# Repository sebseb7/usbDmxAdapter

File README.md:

usbDmxAdapter
=============

usbDmxAdapter

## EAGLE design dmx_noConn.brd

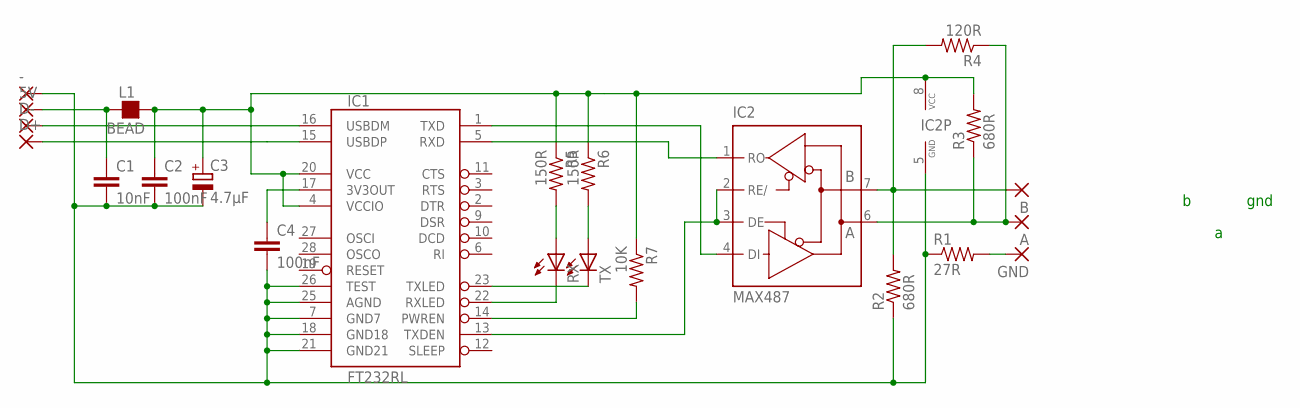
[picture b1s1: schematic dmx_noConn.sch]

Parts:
5V: SMD5; SMD2,54-5,08
-: SMD5; SMD2,54-5,08
A: SMD5; SMD2,54-5,08
B: SMD5; SMD2,54-5,08
C1: 10nF; 0805
C2, C4: 100nF; 0805
C3: 4.7µF; SMC_C
D+: SMD5; SMD2,54-5,08
D-: SMD5; SMD2,54-5,08
GND: SMD5; SMD2,54-5,08
IC1: FT232RL; SSOP28DB
IC2: MAX487; SO08
L1: BEAD; L0805
R1: 27R; 0805
R2, R3: 680R; 0805
R4: 120R; 0805
R5, R6: 150R; 0805
R7: 10K; 0805
RX: LEDCHIP-LED0805; CHIP-LED0805
TX: LEDCHIP-LED0805; CHIP-LED0805

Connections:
+USB_SIEVED: C2.1, C3.+, IC1.4 (VCCIO), IC1.20 (VCC), IC2.8 (VCC), L1.2, R3.2, R5.1, R6.1, R7.1
GND_USB: -.1, C1.2, C2.2, C3.-, C4.2, IC1.7 (GND7), IC1.18 (GND18), IC1.21 (GND21), IC1.25 (AGND), IC1.26 (TEST), IC2.5 (GND), R1.1, R2.1
unnamed: IC1.13 (TXDEN), IC2.2 (RE/), IC2.3 (DE)
unnamed: GND.1, R1.2
unnamed: IC1.5 (RXD), IC2.1 (RO)
unnamed: IC1.1 (TXD), IC2.4 (DI)
unnamed: B.1, IC2.7 (B), R2.2, R4.2
unnamed: A.1, IC2.6 (A), R3.1, R4.1
unnamed: D-.1, IC1.16 (USBDM)
unnamed: D+.1, IC1.15 (USBDP)
unnamed: R5.2, RX.A
unnamed: R6.2, TX.A
unnamed: IC1.22 (RXLED), RX.C
unnamed: IC1.23 (TXLED), TX.C
unnamed: C4.1, IC1.17 (3V3OUT)
unnamed: 5V.1, C1.1, L1.1
unnamed: IC1.14 (PWREN), R7.2

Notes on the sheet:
gnd

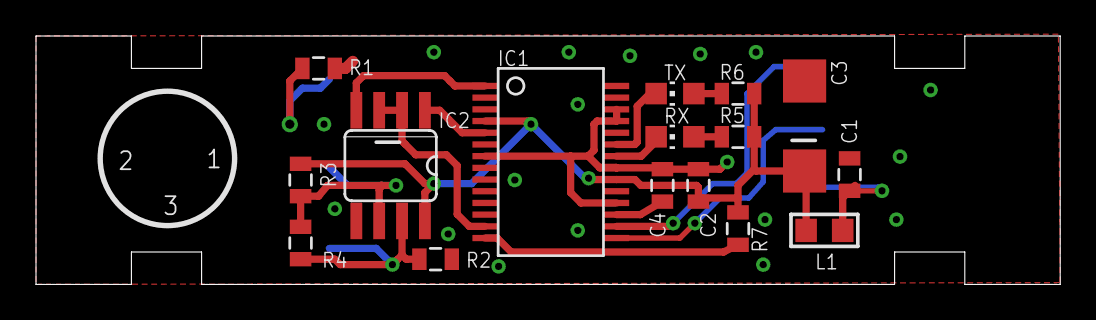
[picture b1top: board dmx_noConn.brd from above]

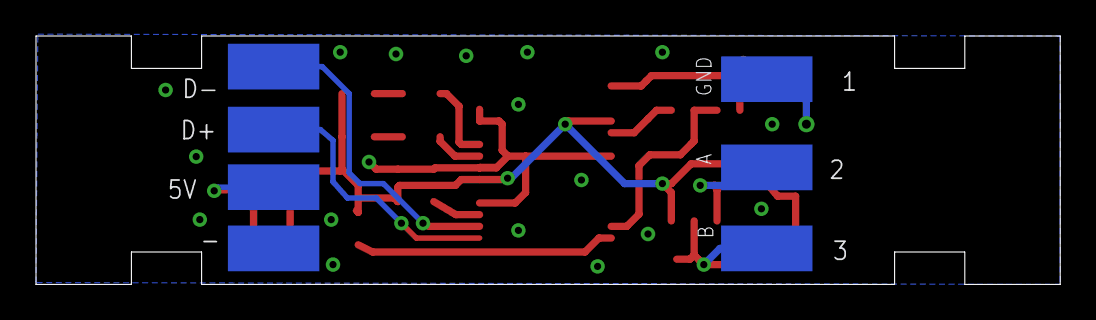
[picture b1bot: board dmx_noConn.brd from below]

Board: 2 copper layers, 56.9 x 13.8 mm, 23 parts (7 on the bottom side), 17 nets.

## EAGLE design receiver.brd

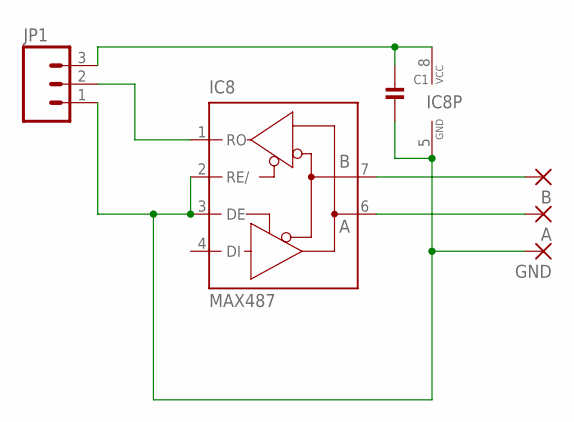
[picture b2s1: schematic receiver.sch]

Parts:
A: SMD5; SMD2,54-5,08
B: SMD5; SMD2,54-5,08
C1: CAP_CERAMIC0805; 0805
GND: SMD5; SMD2,54-5,08
IC8: MAX487; SO08
JP1: M03PTH; 1X03

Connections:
5V: C1.1, IC8.8 (VCC), JP1.3
GND_USB: C1.2, GND.1, IC8.2 (RE/), IC8.3 (DE), IC8.5 (GND), JP1.1
unnamed: B.1, IC8.7 (B)
unnamed: A.1, IC8.6 (A)
TX: IC8.1 (RO), JP1.2

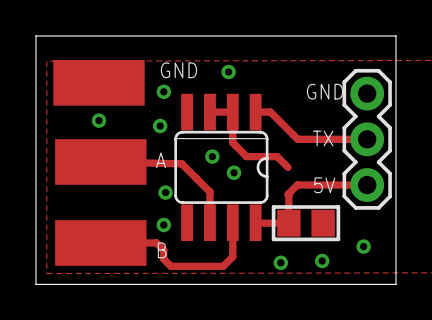
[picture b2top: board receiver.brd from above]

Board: 2 copper layers, 20.0 x 13.8 mm, 6 parts (0 on the bottom side), 5 nets.

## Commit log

2013-01-17 eagle files
2013-01-18 dmx receiver
2013-01-18 removed jp1 text
2013-09-05 proper termination
2013-11-21 no conn version
2013-12-10 minor adjustment

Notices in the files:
parts and their libraries:
SparkFun-Connectors: Licensing: CC v3.0 Share-Alike You are welcome to use this library for commercial purposes.
microbuilder: This work is placed in the public domain, and may be freely used for commercial and non-commercial work with the following conditions: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
